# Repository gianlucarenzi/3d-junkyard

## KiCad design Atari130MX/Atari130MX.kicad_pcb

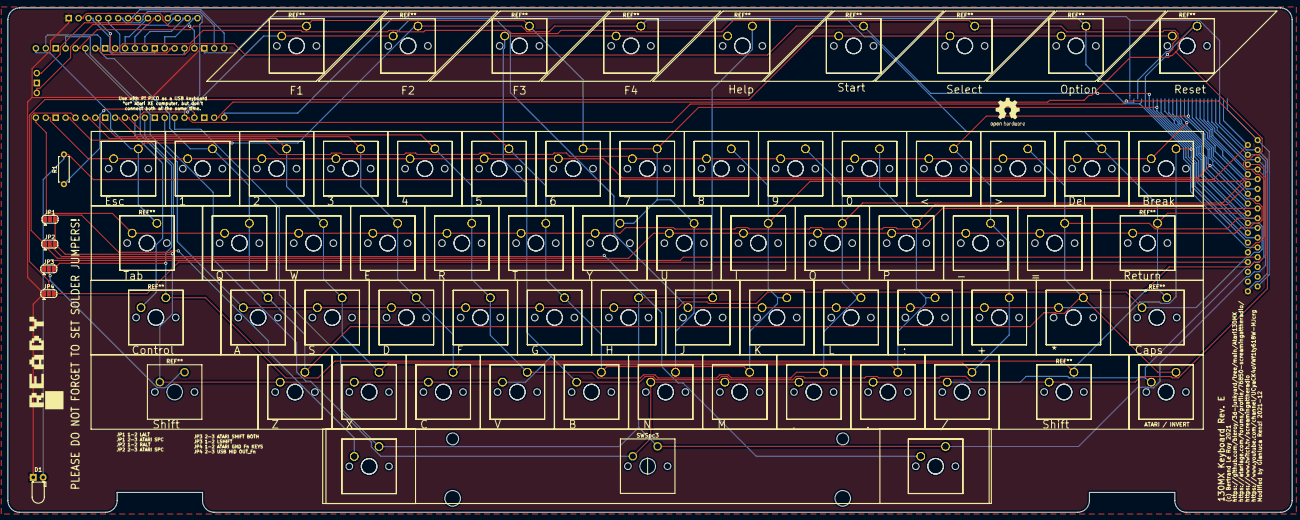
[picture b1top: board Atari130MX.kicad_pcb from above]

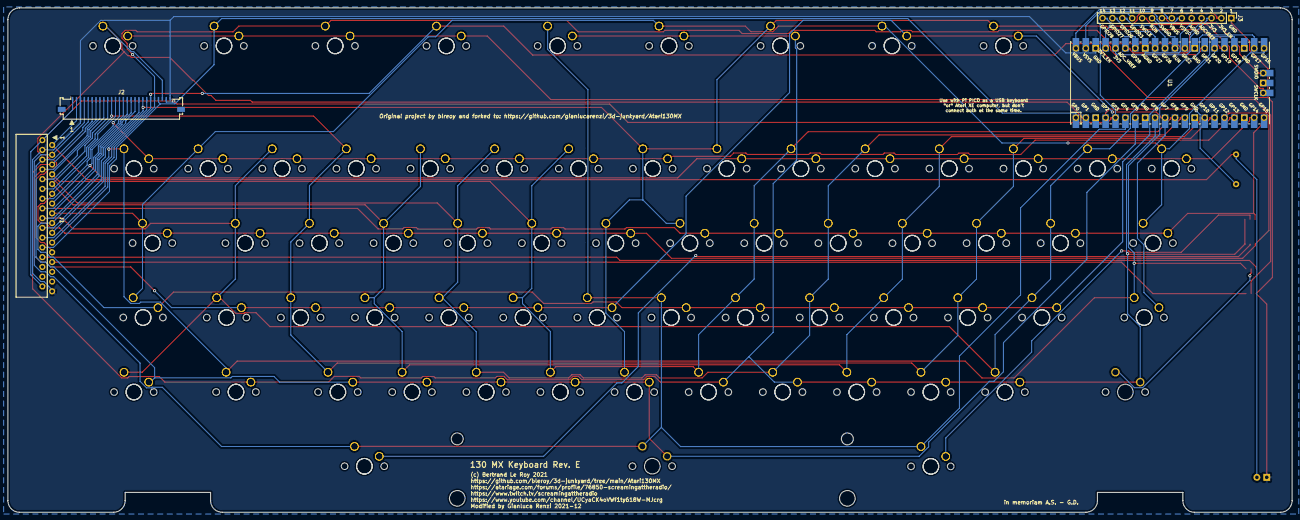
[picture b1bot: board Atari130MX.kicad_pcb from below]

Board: 2 copper layers, 329.2 x 129.3 mm, 79 parts (4 on the bottom side), 43 nets.

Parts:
D1: LED; LED_D3.0mm_Horizontal_O1.27mm_Z2.0mm
J1: Conn_01x32; MOLEX-FFC-1.25mm-RA-52044-3245
J2: Conn_01x26; Molex_200528-0260_1x26-1MP_P1.00mm_Horizontal
J3: Conn_01x14; PinHeader_1x14_P2.54mm_Vertical
JP1, JP2, JP3, JP4: SolderJumper_3_Open; SolderJumper-3_P1.3mm_Open_RoundedPad1.0x1.5mm
L1: LOGO; atari_ready_8mm_rev
R1: R100; R_Axial_DIN0207_L6.3mm_D2.5mm_P7.62mm_Horizontal
SW1, SW2, SW3, SW4, SW5, SW6, SW7, SW8, SW9, SW10: SW_Push_45deg; SW_Kailh_1.00u_PCB
SWA1: SW_Push_45deg; SW_Kailh_1.00u_PCB
SWB1: SW_Push_45deg; SW_Kailh_1.00u_PCB
SWBrk1: SW_Push_45deg; SW_Kailh_1.00u_PCB
SWC1: SW_Push_45deg; SW_Kailh_1.00u_PCB
SWComma1: SW_Push_45deg; SW_Kailh_1.00u_PCB
SWCps1: SW_Push_45deg; SW_Kailh_1.25u_PCB
SWCtl1: SW_Push_45deg; SW_Kailh_1.75u_PCB
SWD1: SW_Push_45deg; SW_Kailh_1.00u_PCB
SWDash1: SW_Push_45deg; SW_Kailh_1.00u_PCB
SWDel1: SW_Push_45deg; SW_Kailh_1.00u_PCB
SWE1: SW_Push_45deg; SW_Kailh_1.00u_PCB
SWEqual1: SW_Push_45deg; SW_Kailh_1.00u_PCB
SWEsc1: SW_Push_45deg; SW_Kailh_1.00u_PCB
SWF1: SW_Push_45deg; SW_Kailh_1.00u_PCB
SWFn1, SWFn2, SWFn3, SWFn4: SW_Push_45deg; SW_Kailh_1.50u_Atari_Fn_PCB
SWG1: SW_Push_45deg; SW_Kailh_1.00u_PCB
SWGT1: SW_Push_45deg; SW_Kailh_1.00u_PCB
SWH1: SW_Push_45deg; SW_Kailh_1.00u_PCB
SWHlp1: SW_Push_45deg; SW_Kailh_1.50u_Atari_Fn_PCB
SWI1: SW_Push_45deg; SW_Kailh_1.00u_PCB
SWInv1: SW_Push_45deg; SW_Kailh_1.00u_PCB
SWJ1: SW_Push_45deg; SW_Kailh_1.00u_PCB
SWK1: SW_Push_45deg; SW_Kailh_1.00u_PCB
SWL1: SW_Push_45deg; SW_Kailh_1.00u_PCB
SWLT1: SW_Push_45deg; SW_Kailh_1.00u_PCB
SWLeftSft1: SW_Push_45deg; SW_Kailh_2.25u_PCB
SWM1: SW_Push_45deg; SW_Kailh_1.00u_PCB
SWN1: SW_Push_45deg; SW_Kailh_1.00u_PCB
SWO1: SW_Push_45deg; SW_Kailh_1.00u_PCB
SWOption1: SW_Push_45deg; SW_Kailh_1.50u_Atari_Fn_PCB
SWP1: SW_Push_45deg; SW_Kailh_1.00u_PCB
SWPeriod1: SW_Push_45deg; SW_Kailh_1.00u_PCB
SWPlus1: SW_Push_45deg; SW_Kailh_1.00u_PCB
SWQ1: SW_Push_45deg; SW_Kailh_1.00u_PCB
SWR1: SW_Push_45deg; SW_Kailh_1.00u_PCB
SWReset1: SW_Push_45deg; SW_Kailh_1.50u_Atari_Fn_PCB
SWRet1: SW_Push_45deg; SW_Kailh_1.50u_PCB
SWRightSft1: SW_Push_45deg; SW_Kailh_1.75u_PCB
SWS1: SW_Push_45deg; SW_Kailh_1.00u_PCB
SWSelect1: SW_Push_45deg; SW_Kailh_1.50u_Atari_Fn_PCB
SWSemi1: SW_Push_45deg; SW_Kailh_1.00u_PCB
SWSlash1: SW_Push_45deg; SW_Kailh_1.00u_PCB
SWSpc1: SW_Push_45deg; SW_Kailh_1.25u_PCB
SWSpc2: SW_Push_45deg; SW_Kailh_1.50u_PCB
SWSpc3: SW_Push_45deg; SW_Cherry_MX1A_6.25u_PCB_3d
SWStar1: SW_Push_45deg; SW_Kailh_1.00u_PCB
SWStart1: SW_Push_45deg; SW_Kailh_1.50u_Atari_Fn_PCB
SWT1: SW_Push_45deg; SW_Kailh_1.00u_PCB
SWTab1: SW_Push_45deg; SW_Kailh_1.50u_PCB
SWU1: SW_Push_45deg; SW_Kailh_1.00u_PCB
SWV1: SW_Push_45deg; SW_Kailh_1.00u_PCB
SWW1: SW_Push_45deg; SW_Kailh_1.00u_PCB
SWX1: SW_Push_45deg; SW_Kailh_1.00u_PCB
SWY1: SW_Push_45deg; SW_Kailh_1.00u_PCB
SWZ1: SW_Push_45deg; SW_Kailh_1.00u_PCB
U1: PICO_RP2040; RPi_Pico_SMD_TH

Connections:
3V3: J3.3, U1.36
3V3_EN: J3.2, U1.37
/LED-GP2: R1.1, U1.4
ADC_VREF: J3.4, U1.35
AGND: J3.5, U1.33
COL_1: J1.19, J2.19, SW1.1, SW2.1, SWFn1.1, SWFn2.1, SWN1.1, SWU1.1, SWY1.1, U1.25
COL_2: J1.4, J2.4, SWH1.1, SWHlp1.1, SWJ1.1, SWSpc1.1, SWSpc2.1, SWSpc3.1, U1.6
COL_3: J1.8, J2.8, SW3.1, SW4.1, SWB1.1, SWG1.1, SWI1.1, SWK1.1, SWM1.1, SWT1.1, U1.11
COL_4: J1.9, J2.9, SW5.1, SW6.1, SWComma1.1, SWF1.1, SWL1.1, SWO1.1, SWR1.1, SWV1.1, U1.12
COL_5: J1.10, J2.10, SW7.1, SW8.1, SWC1.1, SWD1.1, SWE1.1, SWP1.1, SWPeriod1.1, SWSemi1.1, U1.14
COL_6: J1.11, J2.11, SW9.1, SWDash1.1, SWLT1.1, SWPlus1.1, SWS1.1, SWSlash1.1, SWW1.1, SWX1.1, U1.15
COL_7: J1.17, J2.17, SW10.1, SWA1.1, SWEqual1.1, SWGT1.1, SWInv1.1, SWQ1.1, SWStar1.1, SWZ1.1, U1.22
COL_8: J1.16, J2.16, SWCps1.1, SWDel1.1, SWEsc1.1, SWFn3.1, SWFn4.1, SWRet1.1, SWTab1.1, U1.21
COL_9: J1.20, J2.20, JP3.3, SWBrk1.1, SWCtl1.1, SWRightSft1.1, U1.26
GND: D1.1, J1.3, J1.32, J2.3, J2.26, J3.1, JP4.1, U1.38
GPIO26_ADC0: J3.12, U1.31
GPIO27_ADC1: J3.13, U1.32
GPIO28_ADC2: J3.14, U1.34
LED: D1.2, J1.2, J2.2, R1.2
LSC: J1.25, JP3.1
unnamed: JP1.2, SWSpc1.2
unnamed: JP2.2, SWSpc2.2
unnamed: JP3.2, SWLeftSft1.1
unnamed: JP4.2, SWOption1.2, SWReset1.2, SWSelect1.2, SWStart1.2
OPTION: J1.23, J2.23, SWOption1.1, U1.1
OUT_FN: J1.26, JP4.3
POWER: J1.1, J1.31, J2.1, J2.25, J3.11, U1.5
RESET: J1.24, J2.24, SWReset1.1, U1.2
ROW_1: J1.13, J2.13, SW1.2, SW3.2, SW5.2, SW7.2, SWBrk1.2, SWDel1.2, SWGT1.2, SWLT1.2, U1.17
ROW_2: J1.14, J2.14, SW2.2, SW4.2, SW6.2, SW8.2, SW9.2, SW10.2, SWEsc1.2, U1.19
ROW_3: J1.12, J2.12, JP2.1, SWDash1.2, SWEqual1.2, SWI1.2, SWO1.2, SWP1.2, SWRet1.2, SWU1.2, U1.16
ROW_4: J1.15, J2.15, JP1.1, SWE1.2, SWQ1.2, SWR1.2, SWT1.2, SWTab1.2, SWW1.2, SWY1.2, U1.20
ROW_5: J1.7, J2.7, SWCtl1.2, SWFn1.2, SWFn3.2, SWJ1.2, SWK1.2, SWL1.2, SWPlus1.2, SWSemi1.2, SWStar1.2, U1.10
ROW_6: J1.18, J2.18, SWA1.2, SWCps1.2, SWD1.2, SWF1.2, SWG1.2, SWH1.2, SWS1.2, U1.24
ROW_7: J1.5, J2.5, SWComma1.2, SWInv1.2, SWM1.2, SWN1.2, SWPeriod1.2, SWSlash1.2, SWSpc3.2, U1.7
ROW_8: J1.6, J2.6, JP1.3, JP2.3, SWB1.2, SWC1.2, SWFn2.2, SWFn4.2, SWHlp1.2, SWLeftSft1.2, SWRightSft1.2, SWV1.2, SWX1.2, SWZ1.2, U1.9
RUN: J3.9, U1.30
SELECT: J1.22, J2.22, SWSelect1.1, U1.29
START: J1.21, J2.21, SWStart1.1, U1.27
SWCLK: J3.10, U1.41
SWDIO: J3.8, U1.43
VBUS: J3.7, U1.40
VSYS: J3.6, U1.39

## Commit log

2021-12-16 Added footprint and 3d for MOLEX 200528-0260
2021-12-16 Added schematics in PDF
2021-12-16 Added KILIBPATH for RetroBitLab Library
2021-12-16 Added for PCB 5 Pins switches
2021-12-16 RaspberryPi Pico update component
2021-12-16 Modification for RetroBitLab stuff
2021-12-16 Removed some silkscreen garbage
2021-12-16 new dsn
2021-12-16 Added drill map
2021-12-16 New fabrication
2021-12-17 First Fabrication. (Wait for plate finish)
2021-12-17 New drawings (Edge.Cuts) or for new object as keycap hole for 1.25U + 6.25U + 1.50U
2021-12-20 Modified for extra keys (1.25U and 1.50U) at the sides of the standard 6.25U spacebar Removed the original Atari Spacebar as it is not CherryMX compatible. Awating the STL from Axel to include it as 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
    The height of the PLATE + PCB must me adapted depending on which set is built.
    If using original Atari Keycaps with stem adapters for Cherry MX or Kalih switches, the height of the keyboard must be
    lower by 4 millimeters. Some hacks need to be done in the original Atari's case to accomplish that.
    If using the original Atari Keycaps with the modified Kalih switches __AND__ the standard 6.25U + 1.25U + 1.50U switches with Cherry MX, no modifications needed.
    If using
2021-12-20 Updated with Silkscreen logos and mounting holes
